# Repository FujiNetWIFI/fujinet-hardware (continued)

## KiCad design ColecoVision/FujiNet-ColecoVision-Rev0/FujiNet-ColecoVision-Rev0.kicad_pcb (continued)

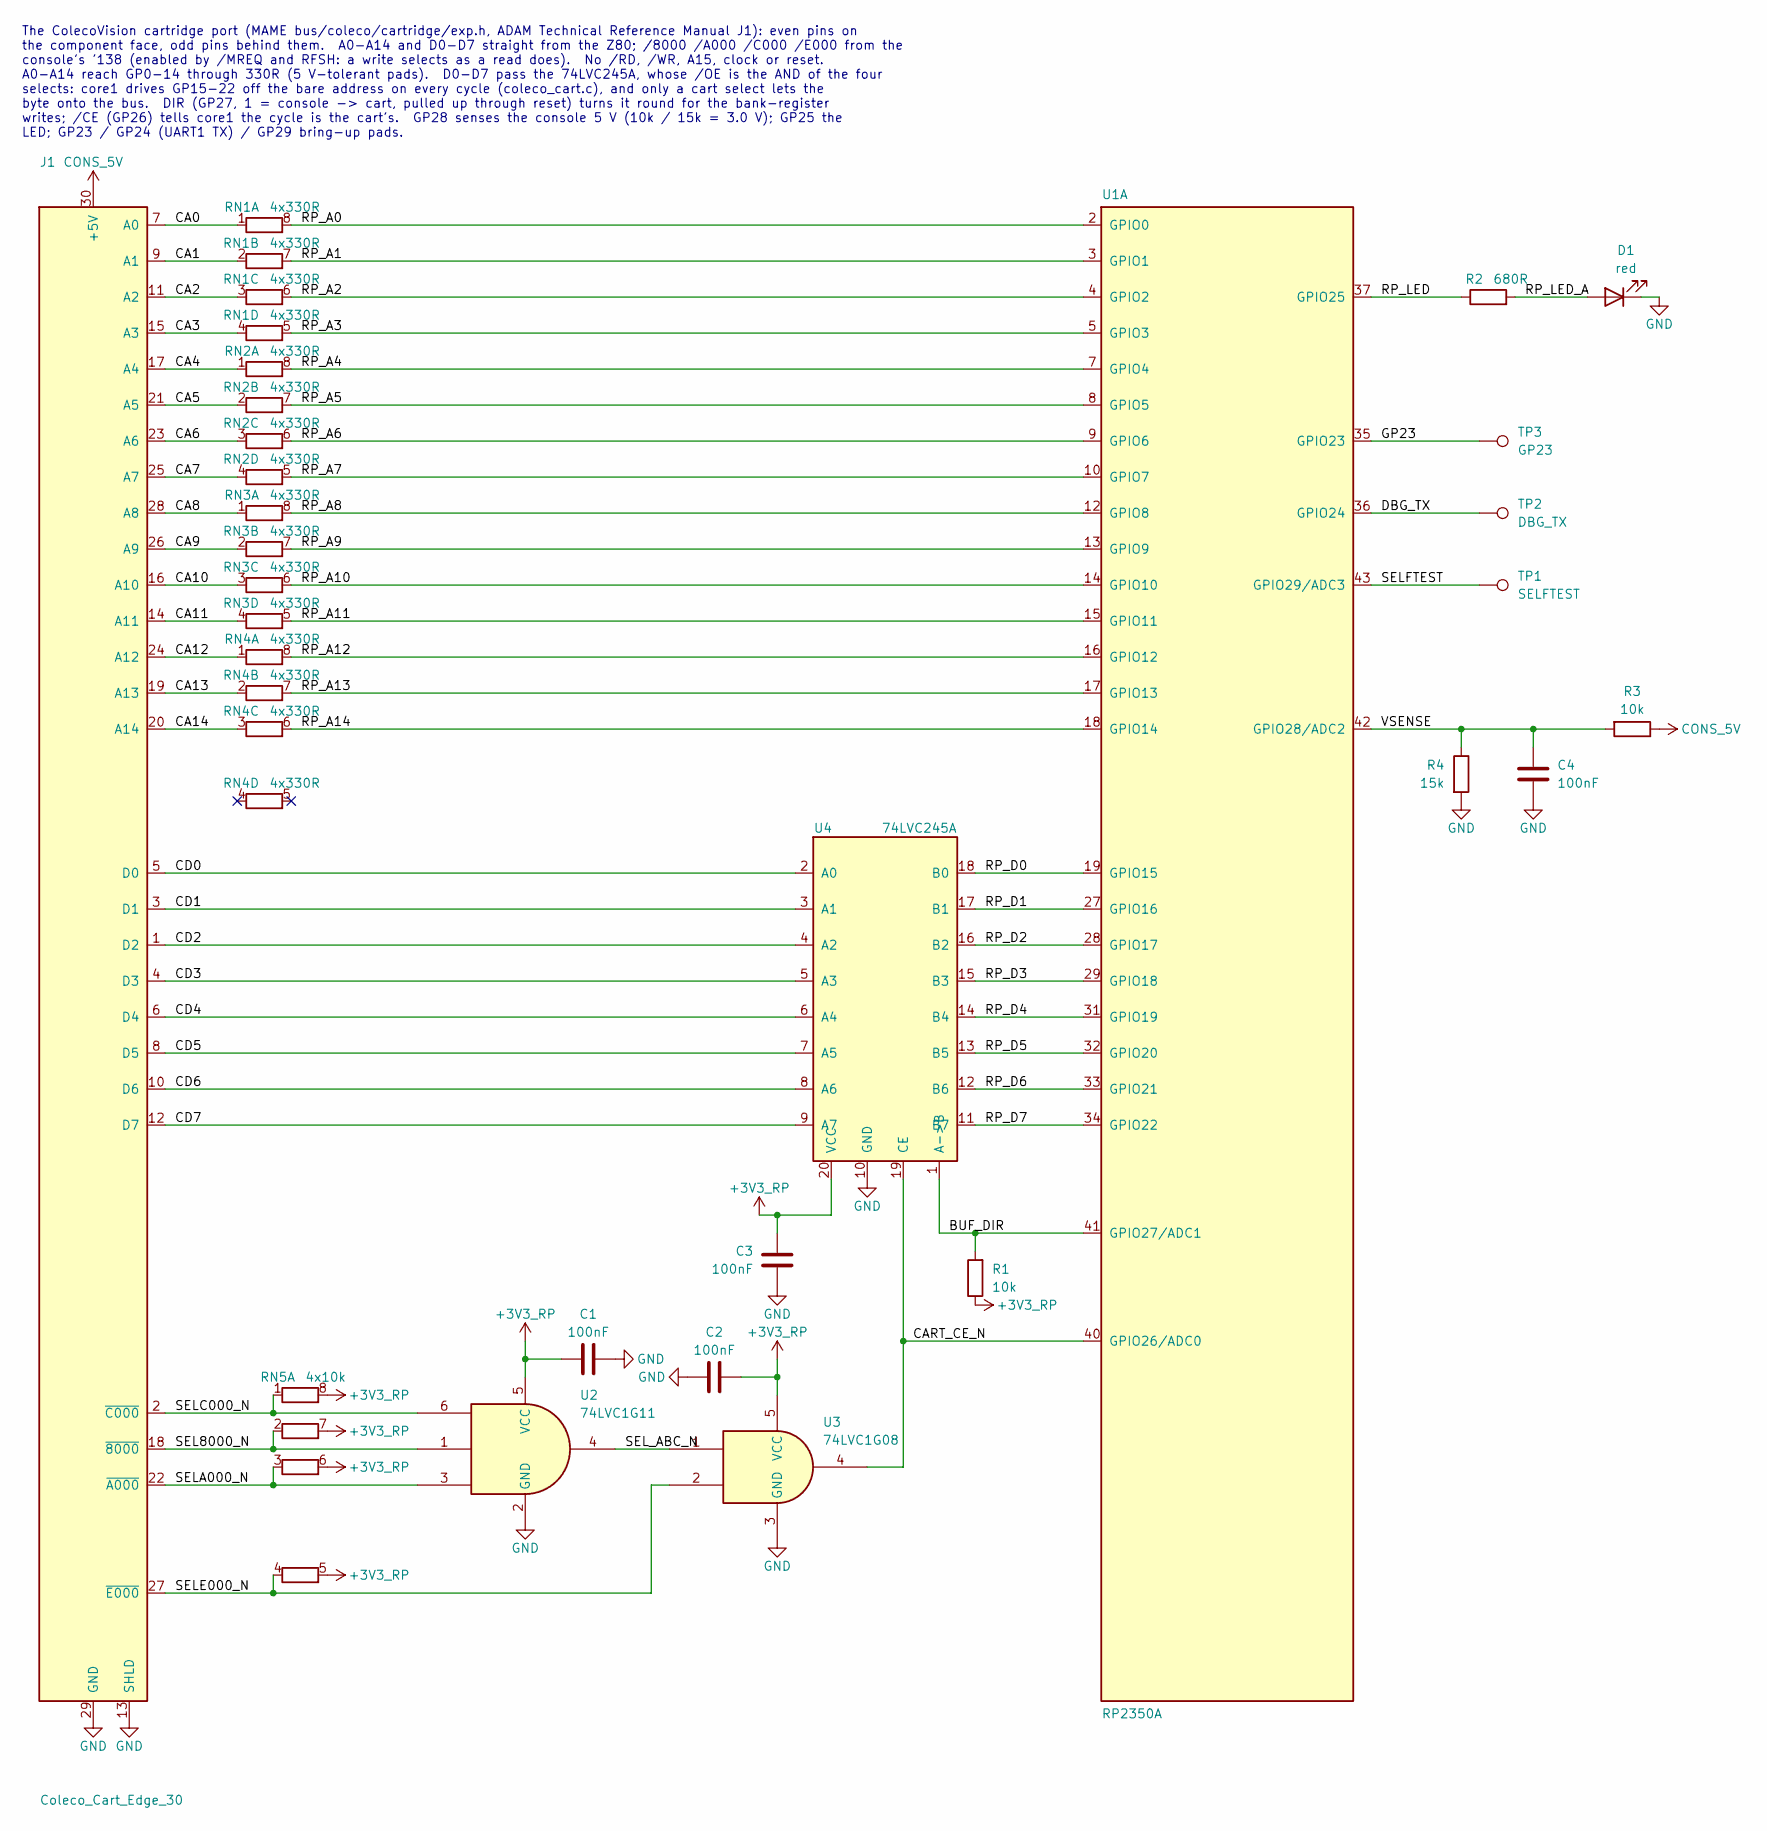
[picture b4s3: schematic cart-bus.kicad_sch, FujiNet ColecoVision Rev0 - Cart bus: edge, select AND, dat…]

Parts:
C1, C2, C3, C4: 100nF; C_0603_1608Metric; MPN CC0603KRX7R9BB104; LCSC C14663
D1: red; LED_0603_1608Metric; MPN KT-0603R; LCSC C2286
J1: Coleco_Cart_Edge_30
R1, R3: 10k; R_0603_1608Metric; MPN 0603WAF1002T5E; LCSC C25804
R2: 680R; R_0603_1608Metric; MPN 0603WAF6800T5E; LCSC C23228
R4: 15k; R_0603_1608Metric; MPN 0603WAF1502T5E; LCSC C22809
RN1, RN2, RN3, RN4: 4x330R; R_Array_Convex_4x0603; MPN 4D03WGJ0331T5E; LCSC C12018
RN5: 4x10k; R_Array_Convex_4x0603; MPN 4D03WGJ0103T5E; LCSC C29718
TP1: SELFTEST; TestPoint_Pad_D1.5mm
TP2: DBG_TX; TestPoint_Pad_D1.5mm
TP3: GP23; TestPoint_Pad_D1.5mm
U1: RP2350A; RPI_RP2350A_QFN60; MPN RP2350A; LCSC C42411118
U2: 74LVC1G11; SOT-23-6; MPN SN74LVC1G11DBVR; LCSC C22046
U3: 74LVC1G08; SOT-23-5; MPN SN74LVC1G08DBVR; LCSC C7666
U4: 74LVC245A; TSSOP-20_4.4x6.5mm_P0.65mm; MPN SN74LVC245APWR; LCSC C7848

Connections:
+3V3_RP: C1.1, C2.1, C3.1, R1.1, RN5.5 (R4.2), RN5.6 (R3.2), RN5.7 (R2.2), RN5.8 (R1.2), U2.5 (VCC), U3.5 (VCC), U4.20 (VCC); also elsewhere on the board
/cart-bus/BUF_DIR: R1.2, U1.41 (GPIO27/ADC1), U4.1 (A->B)
/cart-bus/CA0: J1.7 (A0), RN1.1 (R1.1)
/cart-bus/CA1: J1.9 (A1), RN1.2 (R2.1)
/cart-bus/CA2: J1.11 (A2), RN1.3 (R3.1)
/cart-bus/CA3: J1.15 (A3), RN1.4 (R4.1)
/cart-bus/CA4: J1.17 (A4), RN2.1 (R1.1)
/cart-bus/CA5: J1.21 (A5), RN2.2 (R2.1)
/cart-bus/CA6: J1.23 (A6), RN2.3 (R3.1)
/cart-bus/CA7: J1.25 (A7), RN2.4 (R4.1)
/cart-bus/CA8: J1.28 (A8), RN3.1 (R1.1)
/cart-bus/CA9: J1.26 (A9), RN3.2 (R2.1)
/cart-bus/CA10: J1.16 (A10), RN3.3 (R3.1)
/cart-bus/CA11: J1.14 (A11), RN3.4 (R4.1)
/cart-bus/CA12: J1.24 (A12), RN4.1 (R1.1)
/cart-bus/CA13: J1.19 (A13), RN4.2 (R2.1)
/cart-bus/CA14: J1.20 (A14), RN4.3 (R3.1)
/cart-bus/CART_CE_N: U1.40 (GPIO26/ADC0), U3.4, U4.19 (CE)
/cart-bus/CD0: J1.5 (D0), U4.2 (A0)
/cart-bus/CD1: J1.3 (D1), U4.3 (A1)
/cart-bus/CD2: J1.1 (D2), U4.4 (A2)
/cart-bus/CD3: J1.4 (D3), U4.5 (A3)
/cart-bus/CD4: J1.6 (D4), U4.6 (A4)
/cart-bus/CD5: J1.8 (D5), U4.7 (A5)
/cart-bus/CD6: J1.10 (D6), U4.8 (A6)
/cart-bus/CD7: J1.12 (D7), U4.9 (A7)
/cart-bus/DBG_TX: TP2.1, U1.36 (GPIO24)
/cart-bus/GP23: TP3.1, U1.35 (GPIO23)
/cart-bus/RP_A0: RN1.8 (R1.2), U1.2 (GPIO0)
/cart-bus/RP_A1: RN1.7 (R2.2), U1.3 (GPIO1)
/cart-bus/RP_A2: RN1.6 (R3.2), U1.4 (GPIO2)
/cart-bus/RP_A3: RN1.5 (R4.2), U1.5 (GPIO3)
/cart-bus/RP_A4: RN2.8 (R1.2), U1.7 (GPIO4)
/cart-bus/RP_A5: RN2.7 (R2.2), U1.8 (GPIO5)
/cart-bus/RP_A6: RN2.6 (R3.2), U1.9 (GPIO6)
/cart-bus/RP_A7: RN2.5 (R4.2), U1.10 (GPIO7)
/cart-bus/RP_A8: RN3.8 (R1.2), U1.12 (GPIO8)
/cart-bus/RP_A9: RN3.7 (R2.2), U1.13 (GPIO9)
/cart-bus/RP_A10: RN3.6 (R3.2), U1.14 (GPIO10)
/cart-bus/RP_A11: RN3.5 (R4.2), U1.15 (GPIO11)
/cart-bus/RP_A12: RN4.8 (R1.2), U1.16 (GPIO12)
/cart-bus/RP_A13: RN4.7 (R2.2), U1.17 (GPIO13)
/cart-bus/RP_A14: RN4.6 (R3.2), U1.18 (GPIO14)
/cart-bus/RP_D0: U1.19 (GPIO15), U4.18 (B0)
/cart-bus/RP_D1: U1.27 (GPIO16), U4.17 (B1)
/cart-bus/RP_D2: U1.28 (GPIO17), U4.16 (B2)
/cart-bus/RP_D3: U1.29 (GPIO18), U4.15 (B3)
/cart-bus/RP_D4: U1.31 (GPIO19), U4.14 (B4)
/cart-bus/RP_D5: U1.32 (GPIO20), U4.13 (B5)
/cart-bus/RP_D6: U1.33 (GPIO21), U4.12 (B6)
/cart-bus/RP_D7: U1.34 (GPIO22), U4.11 (B7)
/cart-bus/RP_LED: R2.1, U1.37 (GPIO25)
/cart-bus/RP_LED_A: D1.2 (A), R2.2
/cart-bus/SEL8000_N: J1.18 (~8000), RN5.2 (R2.1), U2.1
/cart-bus/SELA000_N: J1.22 (~A000), RN5.3 (R3.1), U2.3
/cart-bus/SELC000_N: J1.2 (~C000), RN5.1 (R1.1), U2.6
/cart-bus/SELE000_N: J1.27 (~E000), RN5.4 (R4.1), U3.2
/cart-bus/SELFTEST: TP1.1, U1.43 (GPIO29/ADC3)
/cart-bus/SEL_ABC_N: U2.4, U3.1
/cart-bus/VSENSE: C4.1, R3.2, R4.1, U1.42 (GPIO28/ADC2)
CONS_5V: J1.30 (+5V), R3.1; also elsewhere on the board
GND: C1.2, C2.2, C3.2, C4.2, D1.1 (K), J1.13 (SHLD), J1.29 (GND), R4.2, U2.2 (GND), U3.3 (GND), U4.10 (GND); also elsewhere on the board

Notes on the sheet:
The ColecoVision cartridge port (MAME bus/coleco/cartridge/exp.h, ADAM Technical Reference Manual J1): even pins on the component face, odd pins behind them. A0-A14 and D0-D7 straight from the Z80; /8000 /A000 /C000 /E000 from the console's '138 (enabled by /MREQ and RFSH: a write selects as a read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

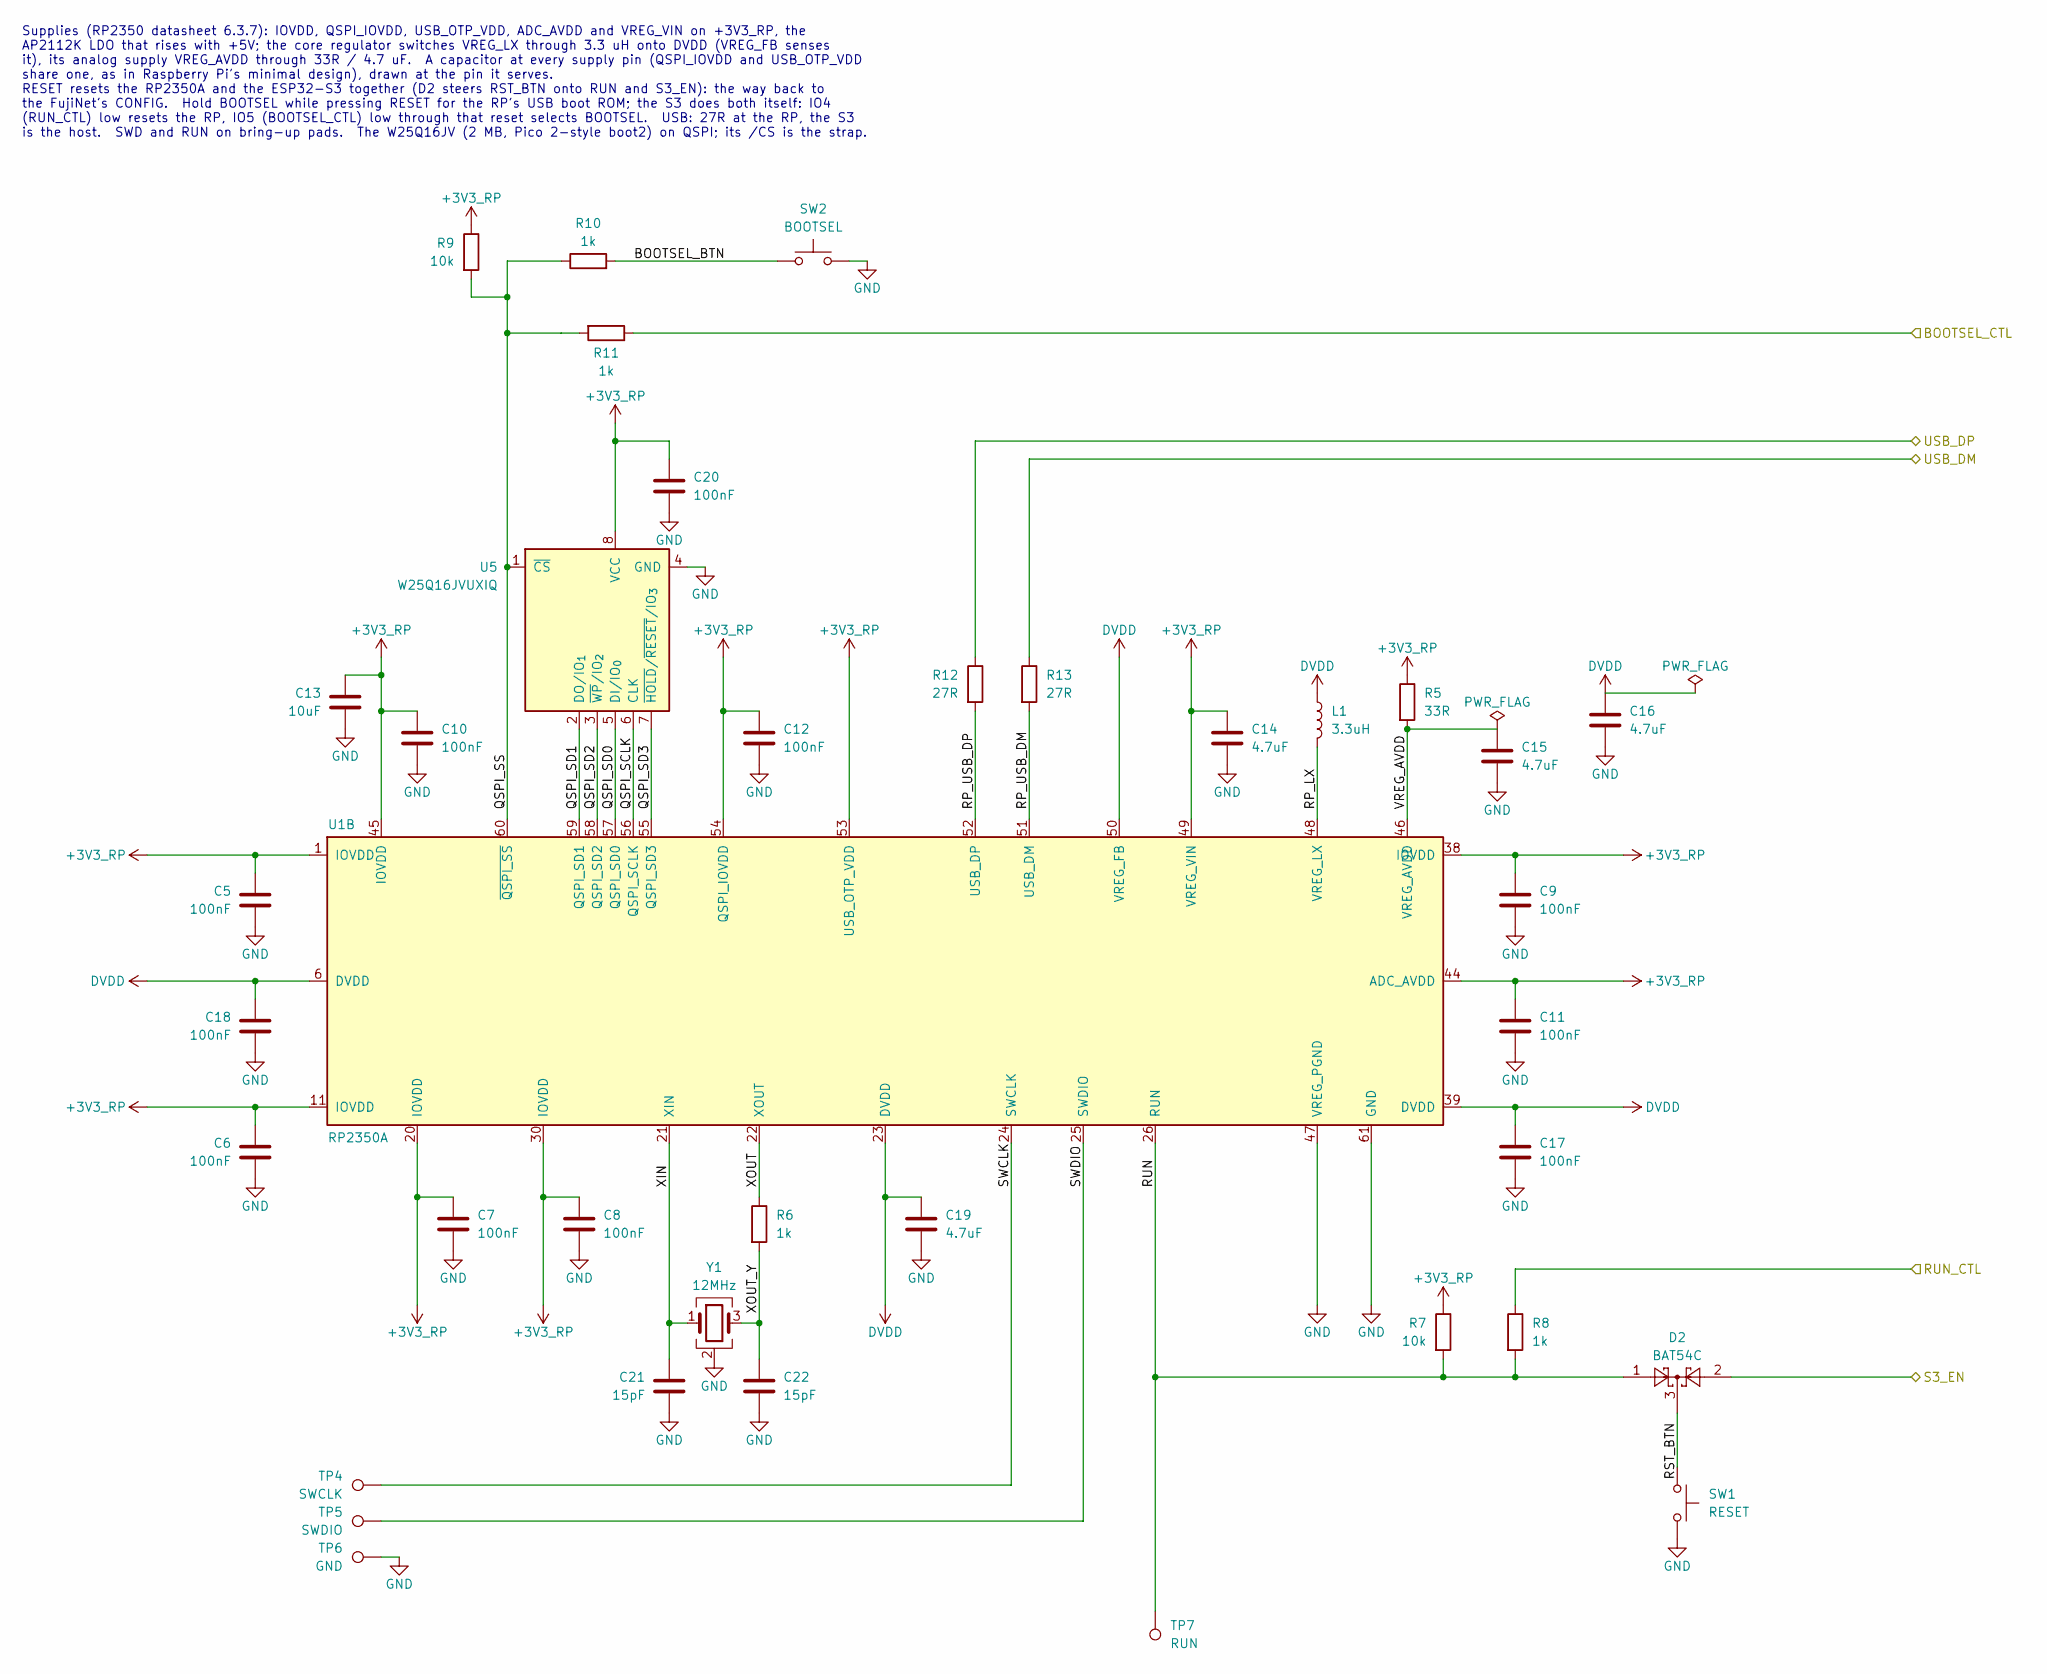
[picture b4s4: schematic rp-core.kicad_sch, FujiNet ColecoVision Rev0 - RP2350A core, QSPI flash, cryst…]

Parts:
C5, C6, C7, C12, C17, C18: 100nF; RPI_C0402; MPN CL05B104KO5NNNC; LCSC C1525
C8, C9, C10, C11, C20: 100nF; C_0603_1608Metric; MPN CC0603KRX7R9BB104; LCSC C14663
C13: 10uF; C_0603_1608Metric; MPN CL10A106KP8NNNC; LCSC C19702
C14, C16: 4.7uF; RPI_C0402_wide; MPN CL05A475MP5NRNC; LCSC C23733
C15, C19: 4.7uF; RPI_C0402; MPN CL05A475MP5NRNC; LCSC C23733
C21, C22: 15pF; C_0603_1608Metric; MPN CL10C150JB8NNNC; LCSC C1644
D2: BAT54C; SOT-23; MPN BAT54C,215; LCSC C37704
L1: 3.3uH; RPI_L_AOTA-B201610S3R3; MPN AOTA-B201610S3R3-101-T; LCSC C42411119
R5: 33R; RPI_R0402; MPN 0402WGF330JTCE; LCSC C25105
R6, R8, R10, R11: 1k; R_0603_1608Metric; MPN 0603WAF1001T5E; LCSC C21190
R7, R9: 10k; R_0603_1608Metric; MPN 0603WAF1002T5E; LCSC C25804
R12, R13: 27R; RPI_R0402; MPN 0402WGF270JTCE; LCSC C25100
SW1: RESET; SW_SPST_TS-1187A; MPN TS-1187A-B-A-B; LCSC C318884
SW2: BOOTSEL; SW_SPST_TS-1187A; MPN TS-1187A-B-A-B; LCSC C318884
TP4: SWCLK; TestPoint_Pad_D1.5mm
TP5: SWDIO; TestPoint_Pad_D1.5mm
TP6: GND; TestPoint_Pad_D1.5mm
TP7: RUN; TestPoint_Pad_D1.5mm
U1: RP2350A; RPI_RP2350A_QFN60; MPN RP2350A; LCSC C42411118
U5: W25Q16JVUXIQ; Winbond_USON-8-1EP_3x2mm_P0.5mm_EP0.2x1.6mm; MPN W25Q16JVUXIQ; LCSC C2843335
Y1: 12MHz; Crystal_SMD_3225-4Pin_3.2x2.5mm; MPN ABM8-272-T3; LCSC C20625731

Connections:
+3V3_RP: C5.1, C6.1, C7.1, C8.1, C9.1, C10.1, C11.1, C12.1, C13.1, C14.1, C20.1, R5.1, R7.1, R9.1, U1.1 (IOVDD), U1.11 (IOVDD), U1.20 (IOVDD), U1.30 (IOVDD), U1.38 (IOVDD), U1.44 (ADC_AVDD), U1.45 (IOVDD), U1.49 (VREG_VIN), U1.53 (USB_OTP_VDD), U1.54 (QSPI_IOVDD), U5.8 (VCC); also elsewhere on the board
/BOOTSEL_CTL: R11.1; also elsewhere on the board
/RUN_CTL: R8.1; also elsewhere on the board
/S3_EN: D2.2; also elsewhere on the board
/USB_DM: R13.1; also elsewhere on the board
/USB_DP: R12.1; also elsewhere on the board
/rp-core/BOOTSEL_BTN: R10.2, SW2.1
/rp-core/QSPI_SCLK: U1.56 (QSPI_SCLK), U5.6 (CLK)
/rp-core/QSPI_SD0: U1.57 (QSPI_SD0), U5.5 (DI/IO_{0})
/rp-core/QSPI_SD1: U1.59 (QSPI_SD1), U5.2 (DO/IO_{1})
/rp-core/QSPI_SD2: U1.58 (QSPI_SD2), U5.3 (~WP/IO_{2})
/rp-core/QSPI_SD3: U1.55 (QSPI_SD3), U5.7 (~HOLD/~RESET/IO_{3})
/rp-core/QSPI_SS: R9.2, R10.1, R11.2, U1.60 (~QSPI_SS), U5.1 (~CS)
/rp-core/RP_LX: L1.2, U1.48 (VREG_LX)
/rp-core/RP_USB_DM: R13.2, U1.51 (USB_DM)
/rp-core/RP_USB_DP: R12.2, U1.52 (USB_DP)
/rp-core/RST_BTN: D2.3, SW1.1
/rp-core/RUN: D2.1, R7.2, R8.2, TP7.1, U1.26 (RUN)
/rp-core/SWCLK: TP4.1, U1.24 (SWCLK)
/rp-core/SWDIO: TP5.1, U1.25 (SWDIO)
/rp-core/VREG_AVDD: C15.1, R5.2, U1.46 (VREG_AVDD)
/rp-core/XIN: C21.1, U1.21 (XIN), Y1.1
/rp-core/XOUT: R6.1, U1.22 (XOUT)
/rp-core/XOUT_Y: C22.1, R6.2, Y1.3
DVDD: C16.1, C17.1, C18.1, C19.1, L1.1, U1.6 (DVDD), U1.23 (DVDD), U1.39 (DVDD), U1.50 (VREG_FB)
GND: C5.2, C6.2, C7.2, C8.2, C9.2, C10.2, C11.2, C12.2, C13.2, C14.2, C15.2, C16.2, C17.2, C18.2, C19.2, C20.2, C21.2, C22.2, SW1.2, SW2.2, TP6.1, U1.47 (VREG_PGND), U1.61 (GND), U5.4 (GND), Y1.2 (G), Y1.4 (G); also elsewhere on the board

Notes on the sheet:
Supplies (RP2350 datasheet 6.3.7): IOVDD, QSPI_IOVDD, USB_OTP_VDD, ADC_AVDD and VREG_VIN on +3V3_RP, the AP2112K LDO that rises with +5V; the core regulator switches VREG_LX through 3.3 uH onto DVDD (VREG_FB senses it), its analog supply VREG_AVDD through 33R / 4.7 uF. A capacitor at every supply p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

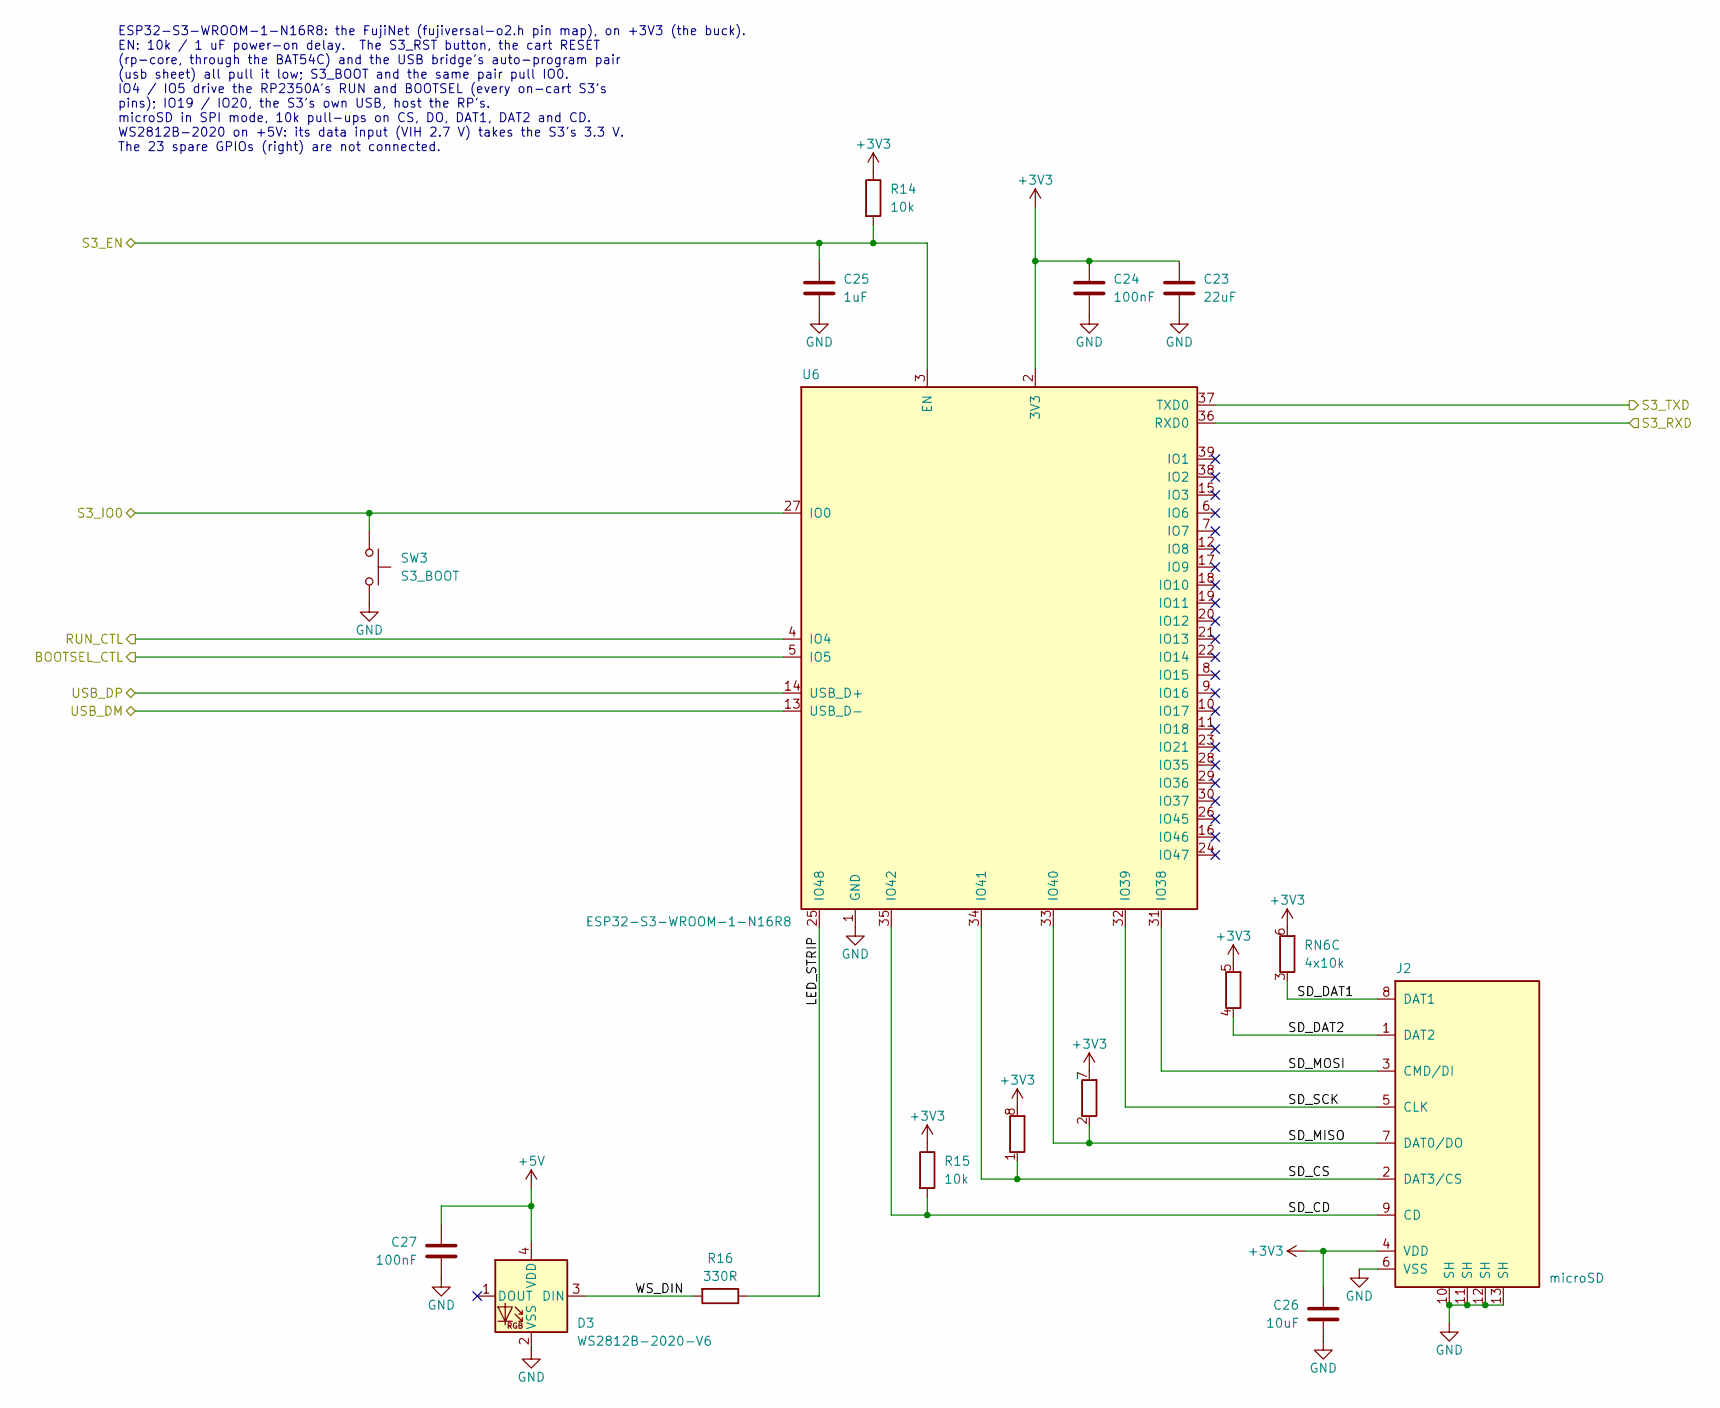
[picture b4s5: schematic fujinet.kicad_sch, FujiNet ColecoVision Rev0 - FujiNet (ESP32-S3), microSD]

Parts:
C23: 22uF; C_0805_2012Metric; MPN CL21A226MAQNNNE; LCSC C45783
C24, C27: 100nF; C_0603_1608Metric; MPN CC0603KRX7R9BB104; LCSC C14663
C25: 1uF; C_0603_1608Metric; MPN CL10A105KB8NNNC; LCSC C15849
C26: 10uF; C_0603_1608Metric; MPN CL10A106KP8NNNC; LCSC C19702
D3: WS2812B-2020-V6; LED_WS2812B-2020_PLCC4_2.0x2.0mm; MPN WS2812B-2020-V6; LCSC C52917434
J2: microSD; TF-SMD_TF-015; MPN TF-015; LCSC C113206
R14, R15: 10k; R_0603_1608Metric; MPN 0603WAF1002T5E; LCSC C25804
R16: 330R; R_0603_1608Metric; MPN 0603WAF3300T5E; LCSC C23138
RN6: 4x10k; R_Array_Convex_4x0603; MPN 4D03WGJ0103T5E; LCSC C29718
SW3: S3_BOOT; SW_SPST_TS-1187A; MPN TS-1187A-B-A-B; LCSC C318884
U6: ESP32-S3-WROOM-1-N16R8; ESP32-S3-WROOM-1; MPN ESP32-S3-WROOM-1-N16R8; LCSC C2913202

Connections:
+3V3: C23.1, C24.1, C26.1, J2.4 (VDD), R14.1, R15.1, RN6.5 (R4.2), RN6.6 (R3.2), RN6.7 (R2.2), RN6.8 (R1.2), U6.2 (3V3); also elsewhere on the board
+5V: C27.1, D3.4 (VDD); also elsewhere on the board
/BOOTSEL_CTL: U6.5 (IO5); also elsewhere on the board
/RUN_CTL: U6.4 (IO4); also elsewhere on the board
/S3_EN: C25.1, R14.2, U6.3 (EN); also elsewhere on the board
/S3_IO0: SW3.1, U6.27 (IO0); also elsewhere on the board
/S3_RXD: U6.36 (RXD0); also elsewhere on the board
/S3_TXD: U6.37 (TXD0); also elsewhere on the board
/USB_DM: U6.13 (USB_D-); also elsewhere on the board
/USB_DP: U6.14 (USB_D+); also elsewhere on the board
/fujinet/LED_STRIP: R16.1, U6.25 (IO48)
/fujinet/SD_CD: J2.9 (CD), R15.2, U6.35 (IO42)
/fujinet/SD_CS: J2.2 (DAT3/CS), RN6.1 (R1.1), U6.34 (IO41)
/fujinet/SD_DAT1: J2.8 (DAT1), RN6.3 (R3.1)
/fujinet/SD_DAT2: J2.1 (DAT2), RN6.4 (R4.1)
/fujinet/SD_MISO: J2.7 (DAT0/DO), RN6.2 (R2.1), U6.33 (IO40)
/fujinet/SD_MOSI: J2.3 (CMD/DI), U6.31 (IO38)
/fujinet/SD_SCK: J2.5 (CLK), U6.32 (IO39)
/fujinet/WS_DIN: D3.3 (DIN), R16.2
GND: C23.2, C24.2, C25.2, C26.2, C27.2, D3.2 (VSS), J2.6 (VSS), J2.10 (SH), J2.11 (SH), J2.12 (SH), J2.13 (SH), SW3.2, U6.1 (GND), U6.40 (GND), U6.41 (GND); also elsewhere on the board

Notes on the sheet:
ESP32-S3-WROOM-1-N16R8: the FujiNet (fujiversal-o2.h pin map), on +3V3 (the buck). EN: 10k / 1 uF power-on delay. The S3_RST button, the cart RESET (rp-core, through the BAT54C) and the USB bridge's auto-program pair (usb sheet) all pull it low; S3_BOOT and the same pair pull IO0. IO4 / IO5 drive t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

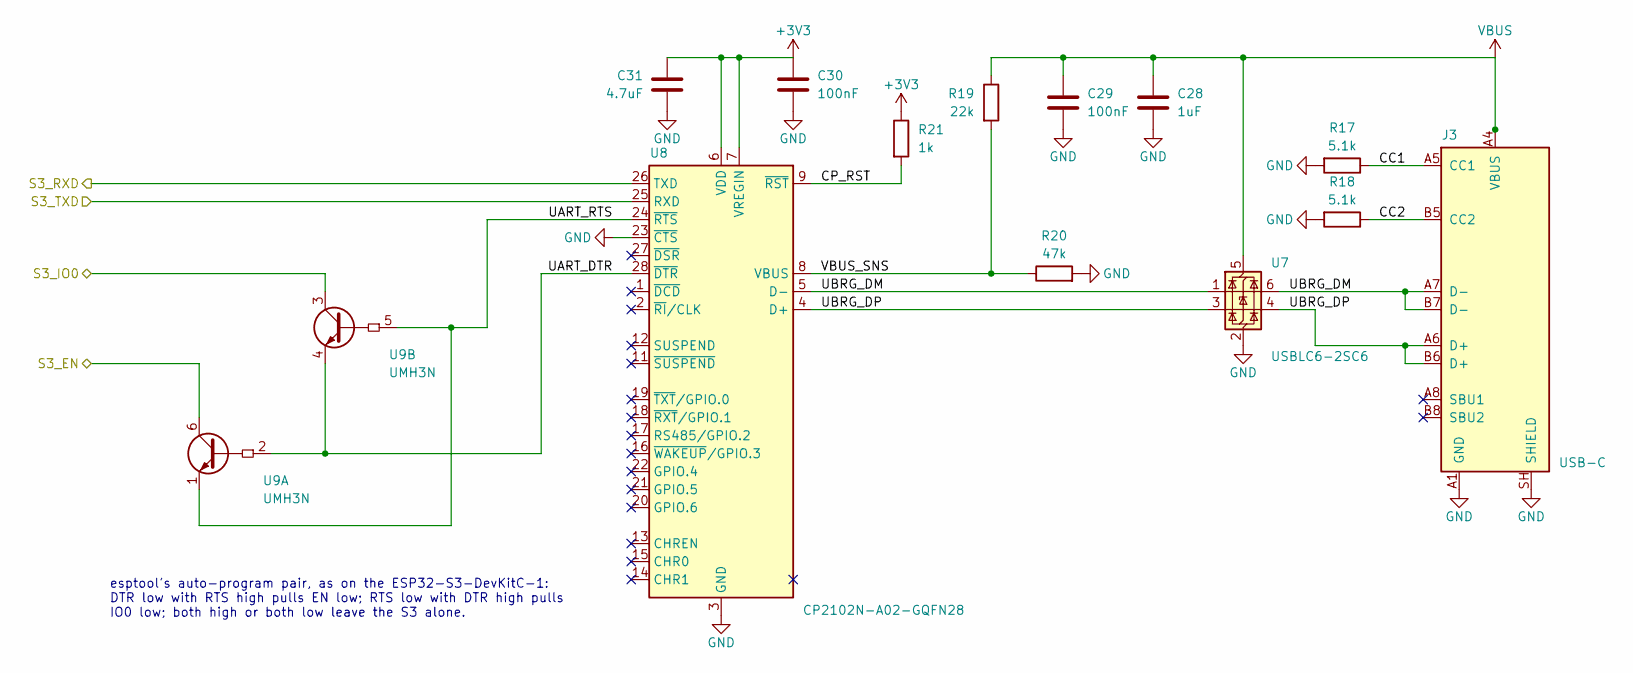
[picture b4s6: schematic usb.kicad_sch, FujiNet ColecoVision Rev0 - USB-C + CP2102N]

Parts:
C28: 1uF; C_0603_1608Metric; MPN CL10A105KB8NNNC; LCSC C15849
C29, C30: 100nF; C_0603_1608Metric; MPN CC0603KRX7R9BB104; LCSC C14663
C31: 4.7uF; C_0603_1608Metric; MPN CL10A475KO8NNNC; LCSC C19666
J3: USB-C; USB_C_Receptacle_HRO_TYPE-C-31-M-12; MPN TYPE-C-31-M-12; LCSC C165948
R17, R18: 5.1k; R_0603_1608Metric; MPN 0603WAF5101T5E; LCSC C23186
R19: 22k; R_0603_1608Metric; MPN 0603WAF2202T5E; LCSC C31850
R20: 47k; R_0603_1608Metric; MPN 0603WAF4702T5E; LCSC C25819
R21: 1k; R_0603_1608Metric; MPN 0603WAF1001T5E; LCSC C21190
U7: USBLC6-2SC6; SOT-23-6; MPN USBLC6-2SC6; LCSC C7519
U8: CP2102N-A02-GQFN28; QFN-28-1EP_5x5mm_P0.5mm_EP3.35x3.35mm; MPN CP2102N-A02-GQFN28R; LCSC C964632
U9: UMH3N; SOT-363_SC-70-6; MPN UMH3N; LCSC C62892

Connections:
+3V3: C30.1, C31.1, R21.1, U8.6 (VDD), U8.7 (VREGIN); also elsewhere on the board
/S3_EN: U9.6 (C1); also elsewhere on the board
/S3_IO0: U9.3 (C2); also elsewhere on the board
/S3_RXD: U8.26 (TXD); also elsewhere on the board
/S3_TXD: U8.25 (RXD); also elsewhere on the board
/usb/CC1: J3.A5 (CC1), R17.1
/usb/CC2: J3.B5 (CC2), R18.1
/usb/CP_RST: R21.2, U8.9 (~RST)
/usb/UART_DTR: U8.28 (~DTR), U9.2 (B1), U9.4 (E2)
/usb/UART_RTS: U8.24 (~RTS), U9.1 (E1), U9.5 (B2)
/usb/UBRG_DM: J3.A7 (D-), J3.B7 (D-), U7.1 (I/O1), U7.6 (I/O1), U8.5 (D-)
/usb/UBRG_DP: J3.A6 (D+), J3.B6 (D+), U7.3 (I/O2), U7.4 (I/O2), U8.4 (D+)
/usb/VBUS_SNS: R19.2, R20.1, U8.8 (VBUS)
GND: C28.2, C29.2, C30.2, C31.2, J3.A1 (GND), J3.A12 (GND), J3.B1 (GND), J3.B12 (GND), J3.SH (SHIELD), R17.2, R18.2, R20.2, U7.2 (GND), U8.3 (GND), U8.23 (~CTS), U8.29 (GND); also elsewhere on the board
VBUS: C28.1, C29.1, J3.A4 (VBUS), J3.A9 (VBUS), J3.B4 (VBUS), J3.B9 (VBUS), R19.1, U7.5 (VBUS); also elsewhere on the board

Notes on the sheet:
esptool's auto-program pair, as on the ESP32-S3-DevKitC-1: DTR low with RTS high pulls EN low; RTS low with DTR high pulls IO0 low; both high or both low leave the S3 alone.

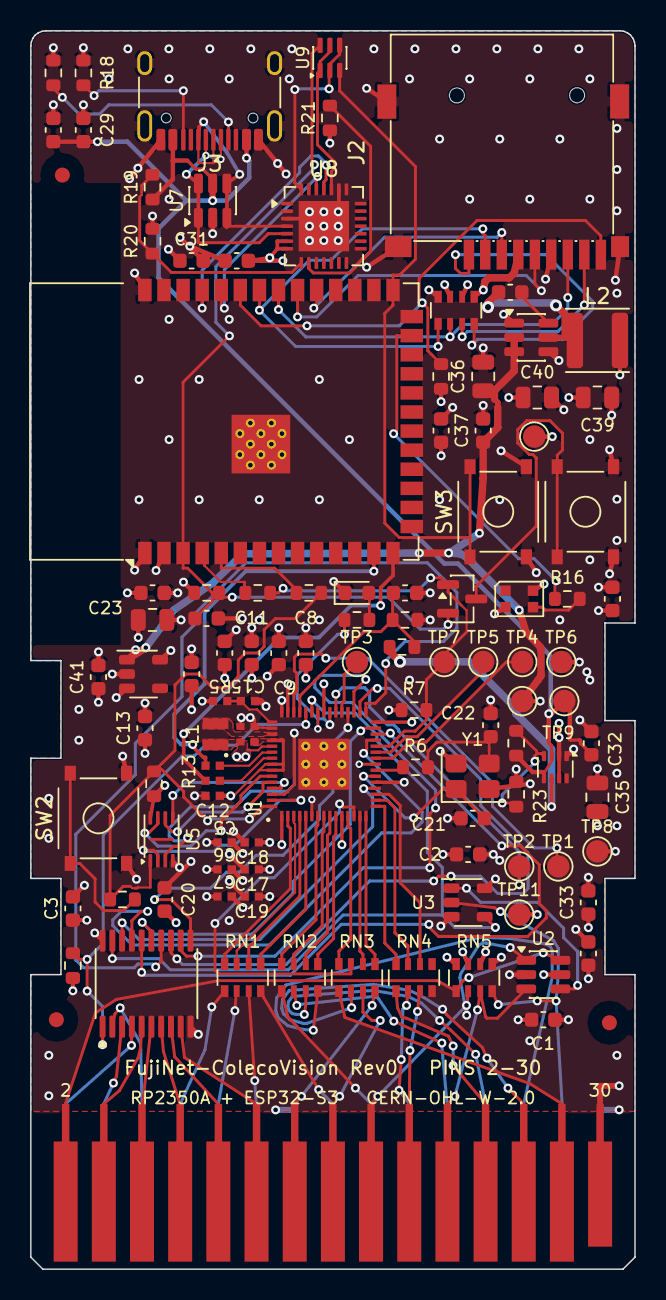
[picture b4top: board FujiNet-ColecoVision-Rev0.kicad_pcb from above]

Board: 4 copper layers, 40.2 x 82.4 mm, 110 parts (0 on the bottom side), 112 nets.

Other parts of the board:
FID1, FID2, FID3: Fiducial_1mm_Mask2mm

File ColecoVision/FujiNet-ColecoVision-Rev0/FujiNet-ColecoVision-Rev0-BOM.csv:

Qty,References,Value,Footprint,MPN,Manufacturer,LCSC,Description,Notes
16,C1 C2 C3 C4 C8 C9 C10 C11 C20 C24 C27 C29 C30 C34 C37 C38,100nF,C_0603_1608Metric,CC0603KRX7R9BB104,YAGEO,C14663,capacitor (several uses: see schematic),
6,C5 C6 C7 C12 C17 C18,100nF,RPI_C0402,CL05B104KO5NNNC,Samsung Electro-Mechanics,C1525,capacitor (several uses: see schematic),
3,C13 C26 C33,10uF,C_0603_1608Metric,CL10A106KP8NNNC,Samsung Electro-Mechanics,C19702,capacitor (several uses: see schematic),
2,C14 C16,4.7uF,RPI_C0402_wide,CL05A475MP5NRNC,Samsung Electro-Mechanics,C23733,capacitor (several uses: see schematic),
2,C15 C19,4.7uF,RPI_C0402,CL05A475MP5NRNC,Samsung Electro-Mechanics,C23733,capacitor (several uses: see schematic),
2,C21 C22,15pF,C_0603_1608Metric,CL10C150JB8NNNC,Samsung Electro-Mechanics,C1644,crystal load,
5,C23 C35 C36 C39 C40,22uF,C_0805_2012Metric,CL21A226MAQNNNE,Samsung Electro-Mechanics,C45783,capacitor (several uses: see schematic),
5,C25 C28 C32 C41 C42,1uF,C_0603_1608Metric,CL10A105KB8NNNC,Samsung Electro-Mechanics,C15849,capacitor (several uses: see schematic),
1,C31,4.7uF,C_0603_1608Metric,CL10A475KO8NNNC,Samsung Electro-Mechanics,C19666,CP2102N VDD bulk,
1,D1,red,LED_0603_1608Metric,KT-0603R,Hubei KENTO Elec,C2286,RP activity LED (GP25),
1,D2,BAT54C,SOT-23,"BAT54C,215",Nexperia,C37704,"RESET steering, common cathode",
1,D3,WS2812B-2020-V6,LED_WS2812B-2020_PLCC4_2.0x2.0mm,WS2812B-2020-V6,Worldsemi,C52917434,status LED on +5V (datasheet VDD 3.7-5.3 V; VIH 2.7 V takes 3.3 V data),
1,J1,Coleco_Cart_Edge_30,Coleco_Cart_Edge_30,,,,"ColecoVision cartridge edge, 2x15 gold fingers, 2.54 mm pitch; odd pins on the back, even pins on the component face",not in BOM
1,J2,microSD,TF-SMD_TF-015,TF-015,SOFNG,C113206,"microSD push-push, SPI mode",
1,J3,USB-C,USB_C_Receptacle_HRO_TYPE-C-31-M-12,TYPE-C-31-M-12,Korean Hroparts Elec,C165948,power + S3 programming / console,
1,L1,3.3uH,RPI_L_AOTA-B201610S3R3,AOTA-B201610S3R3-101-T,Abracon,C42411119,RP2350 core SMPS inductor (polarity marked),
1,L2,6.8uH,L_Sunlord_SWPA4030S,SWPA4030S6R8MT,Sunlord,C62684,buck inductor,
7,R1 R3 R7 R9 R14 R15 R23,10k,R_0603_1608Metric,0603WAF1002T5E,UNI-ROYAL,C25804,resistor (several uses: see schematic),
1,R2,680R,R_0603_1608Metric,0603WAF6800T5E,UNI-ROYAL,C23228,LED series (~2 mA),
1,R4,15k,R_0603_1608Metric,0603WAF1502T5E,UNI-ROYAL,C22809,console 5V sense divider (0.6 x CONS_5V),
1,R5,33R,RPI_R0402,0402WGF330JTCE,UNI-ROYAL,C25105,VREG_AVDD RC filter (R_FILT),
5,R6 R8 R10 R11 R21,1k,R_0603_1608Metric,0603WAF1001T5E,UNI-ROYAL,C21190,resistor (several uses: see schematic),
2,R12 R13,27R,RPI_R0402,0402WGF270JTCE,UNI-ROYAL,C25100,USB series,
1,R16,330R,R_0603_1608Metric,0603WAF3300T5E,UNI-ROYAL,C23138,WS2812 data series,
2,R17 R18,5.1k,R_0603_1608Metric,0603WAF5101T5E,UNI-ROYAL,C23186,UFP Rd,
1,R19,22k,R_0603_1608Metric,0603WAF2202T5E,UNI-ROYAL,C31850,VBUS sense divider,
1,R20,47k,R_0603_1608Metric,0603WAF4702T5E,UNI-ROYAL,C25819,VBUS sense divider,
1,R22,33k,R_0603_1608Metric,0603WAF3302T5E,UNI-ROYAL,C4216,mux priority threshold (VBUS > 4.3 V),
4,RN1 RN2 RN3 RN4,4x330R,R_Array_Convex_4x0603,4D03WGJ0331T5E,UNI-ROYAL,C12018,RN (several uses: see schematic),
2,RN5 RN6,4x10k,R_Array_Convex_4x0603,4D03WGJ0103T5E,UNI-ROYAL,C29718,RN (several uses: see schematic),
1,SW1,RESET,SW_SPST_TS-1187A,TS-1187A-B-A-B,XKB Connection,C318884,cart RESET: RP RUN + S3 EN through the BAT54C,
1,SW2,BOOTSEL,SW_SPST_TS-1187A,TS-1187A-B-A-B,XKB Connection,C318884,RP2350A BOOTSEL (hold while pressing RESET),
1,SW3,S3_BOOT,SW_SPST_TS-1187A,TS-1187A-B-A-B,XKB Connection,C318884,ESP32-S3 BOOT (IO0),
1,TP1,SELFTEST,TestPoint_Pad_D1.5mm,,,,"test pad: GP29, a self-test trigger for bring-up",not in BOM
1,TP2,DBG_TX,TestPoint_Pad_D1.5mm,,,,"test pad: GP24 (UART1 TX), debug UART (3.3 V)",not in BOM
1,TP3,GP23,TestPoint_Pad_D1.5mm,,,,"test pad: GP23, spare",not in BOM
1,TP4,SWCLK,TestPoint_Pad_D1.5mm,,,,test pad,not in BOM
1,TP5,SWDIO,TestPoint_Pad_D1.5mm,,,,test pad,not in BOM
1,TP6,GND,TestPoint_Pad_D1.5mm,,,,test pad,not in BOM
1,TP7,RUN,TestPoint_Pad_D1.5mm,,,,test pad,not in BOM
1,TP8,CONS_5V,TestPoint_Pad_D1.5mm,,,,bring-up pad: console 5V (edge pin 30),not in BOM
1,TP9,VBUS,TestPoint_Pad_D1.5mm,,,,bring-up pad: USB VBUS,not in BOM
1,TP10,+5V,TestPoint_Pad_D1.5mm,,,,bring-up pad: +5V (mux output),not in BOM
1,TP11,+3V3_RP,TestPoint_Pad_D1.5mm,,,,bring-up pad: +3V3_RP (RP LDO),not in BOM
1,TP12,+3V3,TestPoint_Pad_D1.5mm,,,,bring-up pad: +3V3 (buck: S3 side),not in BOM
1,U1,RP2350A,RPI_RP2350A_QFN60,RP2350A,Raspberry Pi,C42411118,RP2350A: serves the ColecoVision cart bus (fujicoleco),
1,U2,74LVC1G11,SOT-23-6,SN74LVC1G11DBVR,Texas Instruments,C22046,select AND: /8000 . /A000 . /C000,
1,U3,74LVC1G08,SOT-23-5,SN74LVC1G08DBVR,Texas Instruments,C7666,select AND: . /E000 = /CE (GP26 and the buffer /OE),
1,U4,74LVC245A,TSSOP-20_4.4x6.5mm_P0.65mm,SN74LVC245APWR,Texas Instruments,C7848,"data buffer, 5V-tolerant at 3.3V: edge D0-D7 <-> GP15-22",
1,U5,W25Q16JVUXIQ,Winbond_USON-8-1EP_3x2mm_P0.5mm_EP0.2x1.6mm,W25Q16JVUXIQ,Winbond,C2843335,2 MB QSPI boot flash,
1,U6,ESP32-S3-WROOM-1-N16R8,ESP32-S3-WROOM-1,ESP32-S3-WROOM-1-N16R8,Espressif,C2913202,FujiNet core (fujiversal-coleco),
1,U7,USBLC6-2SC6,SOT-23-6,USBLC6-2SC6,STMicroelectronics,C7519,"USB ESD: D+, D-, VBUS",
1,U8,CP2102N-A02-GQFN28,QFN-28-1EP_5x5mm_P0.5mm_EP3.35x3.35mm,CP2102N-A02-GQFN28R,Silicon Labs,C964632,USB-UART for S3 flashing/console (self-powered),
1,U9,UMH3N,SOT-363_SC-70-6,UMH3N,Jiangsu Changjing (JSCJ),C62892,esptool auto-program (DevKitC-1 style),
1,U10,TPS2116,SOT-583-8,TPS2116DRLR,Texas Instruments,C3235557,"power mux: VBUS first, console 5V second",
1,U11,AP63203WU,TSOT-23-6,AP63203WU-7,Diodes Incorporated,C780769,"3.3V 2A buck (S3, SD, CP2102N)",
1,U12,AP2112K-3.3,SOT-23-5,AP2112K-3.3TRG1,Diodes Incorporated,C51118,"RP2350A 3.3V LDO (IOVDD, VREG_VIN, VREG_AVDD, flash, bus logic), 600mA, fast start",
1,Y1,12MHz,Crystal_SMD_3225-4Pin_3.2x2.5mm,ABM8-272-T3,Abracon,C20625731,RP2350 12 MHz crystal,

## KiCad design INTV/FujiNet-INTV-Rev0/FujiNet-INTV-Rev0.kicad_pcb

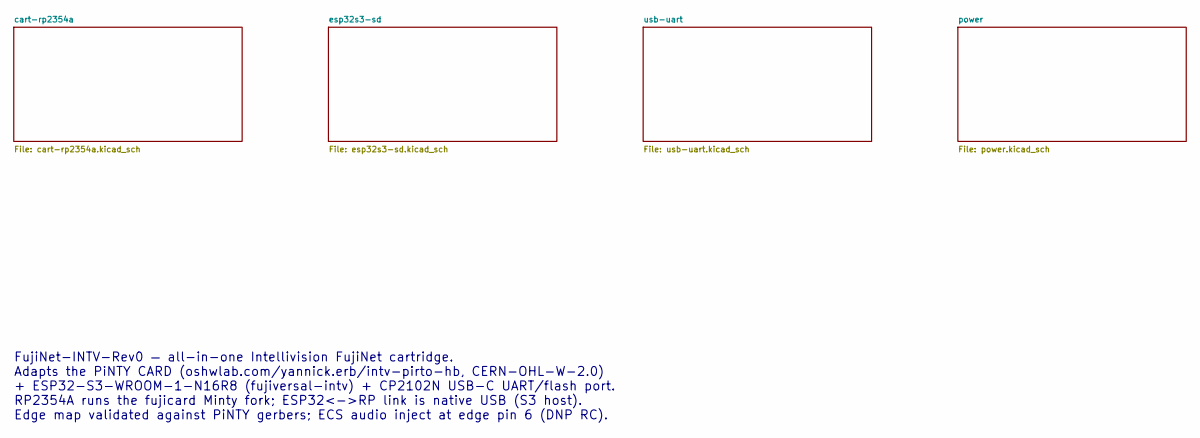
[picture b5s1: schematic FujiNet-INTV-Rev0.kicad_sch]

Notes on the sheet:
FujiNet-INTV-Rev0 — all-in-one Intellivision FujiNet cartridge. Adapts the PiNTY CARD (oshwlab.com/yannick.erb/intv-pirto-hb, CERN-OHL-W-2.0) + ESP32-S3-WROOM-1-N16R8 (fujiversal-intv) + CP2102N USB-C UART/flash port. RP2354A runs the fujicard Minty fork; ESP32<->RP link is native USB (S3 host). Ed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
